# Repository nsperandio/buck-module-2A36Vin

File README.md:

# Buck DC/DC Module [Imax=2A, Vinmax=36V, Vo=5V]
Simple DC/DC converter in an simple and usable form-factor for educational or hobbyist purposes - but still with decent EMI performance and efficiency.

>⚠️ **Work in Progress**  
This design is currently under development and has not yet been fully validated.

## Current Project Status

- [x] Basic schematic
- [x] PCB layout
- [ ] BOM 
- [ ] First prototype assembly
- [ ] Electrical validation
- [ ] Thermal characterization

## Overview
The design is based on the [LV14240](https://www.ti.com/product/LV14240) buck controller with integrated switch by Texas Instruments.

Layout is based on the "Application and Implementation" section of the datasheet.

## Specifications
|Spec|Value|
|-|-|
|Topology | buck (non-synchronous!)|
|Input Voltage| 4 - 36 V|
|Output Voltage| 5 V |
|Maximum Output Current| 2 A |
| Switching frequency| 500 kHz|

## EMI Considerations

An LCR input filter is added to attenuate conducted emissions at the switching frequency. The filter's damping factor can be obtained thanks to the ESR of the bulk capacitor and the DCR of the inductor. If the parasitics are not high enough an additional resistor can be used. 
The following plots refer to the components in the table. Modulus of the buck input impedance in green, modulus of the filter impedance in red:

|Spec|Value|
|-|-|
|Input Inductance| 47 uH|
|Inductors DCR| 230 mOhm|
|Bulk Capacitor| 20 uF |
|Capacitor ESR| 40 mOhm|
|Resonant peak frequency| 4.5 kHz|

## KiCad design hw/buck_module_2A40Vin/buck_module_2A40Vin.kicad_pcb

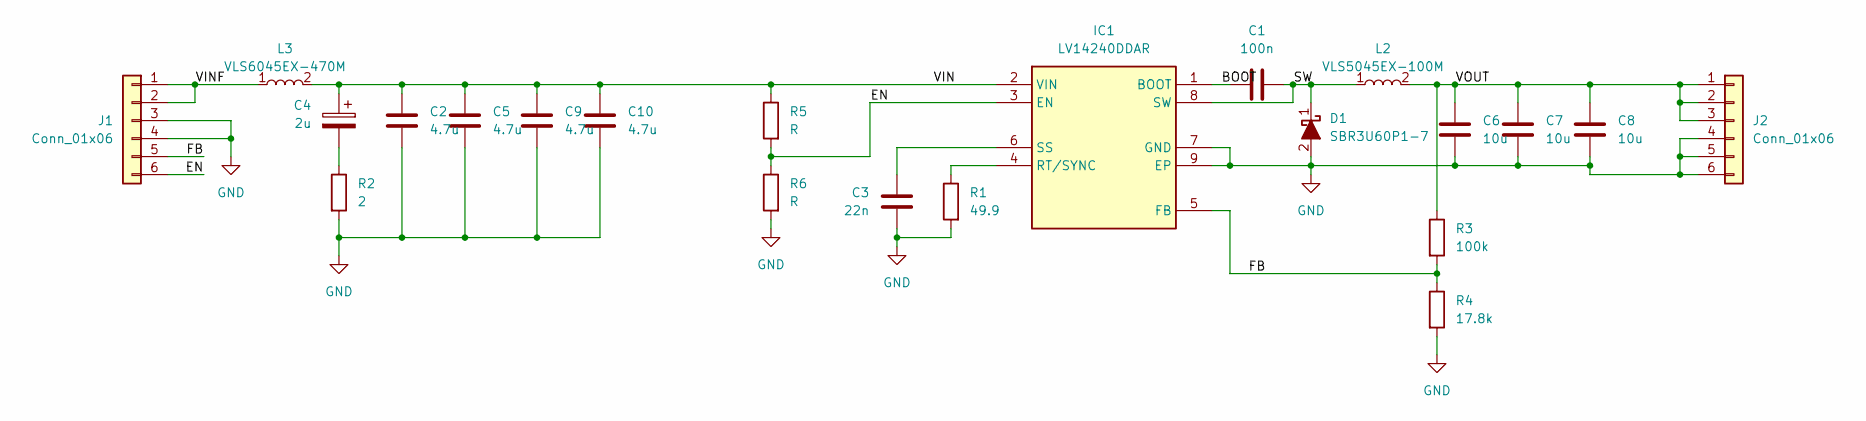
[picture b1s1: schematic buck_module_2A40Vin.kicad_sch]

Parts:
C1: 100n; C_0603_1608Metric; Voltage 16
C2, C5, C9, C10: 4.7u; C_0805_2012Metric; Voltage 100
C3: 22n; C_0603_1608Metric
C4: 2u; CP_Elec_4x5.4
C6: 10u; C_0805_2012Metric; Voltage 16
C7, C8: 10u; C_0805_2012Metric; Voltage 16V
D1: SBR3U60P1-7; SBR3U60P17; Mouser Part Number 621-SBR3U60P1-7
IC1: LV14240DDAR; SOIC127P600X170-9N; Manufacturer_Part_Number LV14240DDAR
J1, J2: Conn_01x06; PinHeader_1x06_P2.54mm_Vertical
L2: VLS5045EX-100M; VLS5045EX330M; Mouser Part Number 810-VLS5045EX-100M
L3: VLS6045EX-470M; VLS6045; Mouser Part Number 810-VLS6045EX-470M
R1: 49.9; R_0603_1608Metric
R2: 2; R_0805_2012Metric
R3: 100k; R_0603_1608Metric
R4: 17.8k; R_0603_1608Metric
R5, R6: R; R_0603_1608Metric

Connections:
/BOOT: C1.1, IC1.1 (BOOT)
/EN: IC1.3 (EN), J1.6, R5.2, R6.1
/FB: IC1.5 (FB), J1.5, R3.2, R4.1
/SW: C1.2, D1.1 (K), IC1.8 (SW), L2.1
/VIN: C2.2, C4.1, C5.2, C9.2, C10.2, IC1.2 (VIN), L3.2, R5.1
/VINF: J1.1, J1.2, L3.1
/VOUT: C6.2, C7.2, C8.2, J2.1, J2.2, J2.3, L2.2, R3.1
GND: C2.1, C3.1, C5.1, C6.1, C7.1, C8.1, C9.1, C10.1, D1.2 (A), IC1.7 (GND), IC1.9 (EP), J1.3, J1.4, J2.4, J2.5, J2.6, R1.2, R2.2, R4.2, R6.2
unnamed: C4.2, R2.1
unnamed: IC1.4 (RT/SYNC), R1.1
unnamed: C3.2, IC1.6 (SS)

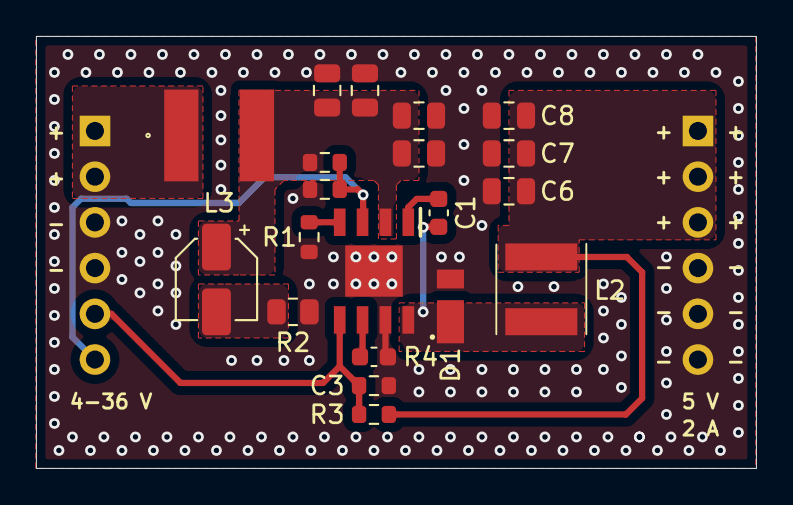
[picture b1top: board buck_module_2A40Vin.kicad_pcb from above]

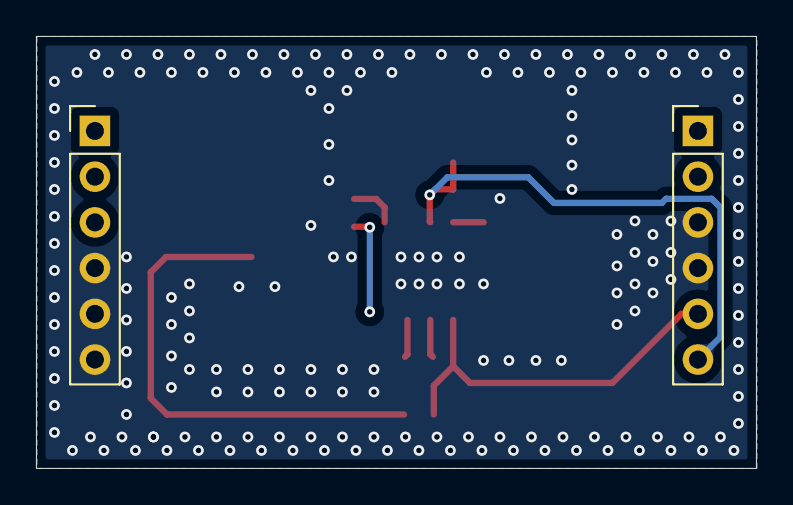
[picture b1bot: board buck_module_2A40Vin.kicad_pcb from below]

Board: 2 copper layers, 40.0 x 24.0 mm, 22 parts (2 on the bottom side), 11 nets.

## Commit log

2026-02-27 Added PCB (schematics, layout, rev0.1)
2026-02-27 Added silkscreen markings on the PCB
2026-02-28 Update README.md
    added input filter transfer function image
2026-02-28 Added Simplis simulation for input filter design
2026-03-02 added schematics in readme
